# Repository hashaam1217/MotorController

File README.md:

# Cleaning up electronics

- Using Pin Sockets so we can reuse components
- We can switch between 8 and 64 Microsteps
-

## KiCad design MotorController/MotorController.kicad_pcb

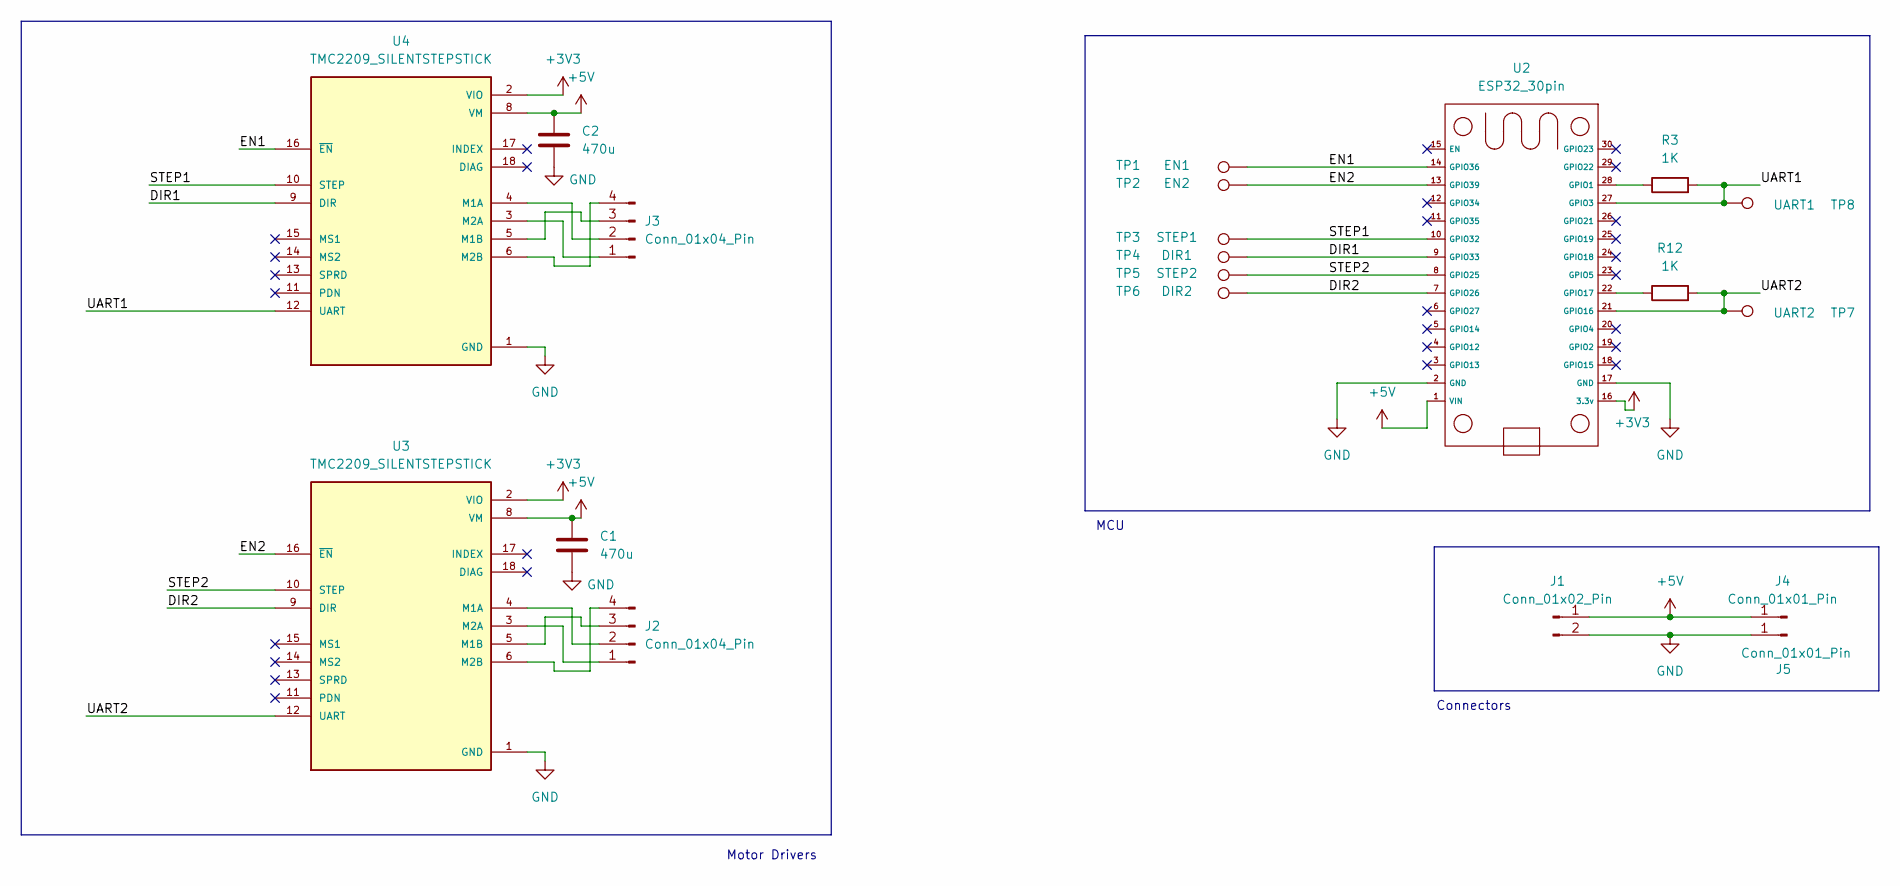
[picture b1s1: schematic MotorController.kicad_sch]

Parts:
C1, C2: 470u; CP_Radial_D6.3mm_P2.50mm
J1: Conn_01x02_Pin; PinSocket_1x02_P2.54mm_Vertical
J2, J3: Conn_01x04_Pin; PinHeader_1x04_P2.54mm_Vertical
J4, J5: Conn_01x01_Pin; PinSocket_1x01_P2.54mm_Vertical
R3, R12: 1K; R_Axial_DIN0617_L17.0mm_D6.0mm_P5.08mm_Vertical
TP1: EN1; TestPoint_Pad_2.0x2.0mm
TP2: EN2; TestPoint_Pad_2.0x2.0mm
TP3: STEP1; TestPoint_Pad_2.0x2.0mm
TP4: DIR1; TestPoint_Pad_2.0x2.0mm
TP5: STEP2; TestPoint_Pad_2.0x2.0mm
TP6: DIR2; TestPoint_Pad_2.0x2.0mm
TP7: UART2; TestPoint_Pad_2.0x2.0mm
TP8: UART1; TestPoint_Pad_2.0x2.0mm
U2: ESP32_30pin
U3, U4: TMC2209_SILENTSTEPSTICK; MODULE_TMC2209_SILENTSTEPSTICK; PARTREV 1.20

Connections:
+3V3: U2.16 (3.3v), U3.2 (VIO), U4.2 (VIO)
+5V: C1.1, C2.1, J1.1, J4.1 (Pin_1_1), U2.1 (VIN), U3.8 (VM), U4.8 (VM)
/DIR1: TP4.1 (1_1), U2.9 (GPIO33), U4.9 (DIR)
/DIR2: TP6.1 (1_1), U2.7 (GPIO26), U3.9 (DIR)
/EN1: TP1.1 (1_1), U2.14 (GPIO36), U4.16 (~EN)
/EN2: TP2.1 (1_1), U2.13 (GPIO39), U3.16 (~EN)
/STEP1: TP3.1 (1_1), U2.10 (GPIO32), U4.10 (STEP)
/STEP2: TP5.1 (1_1), U2.8 (GPIO25), U3.10 (STEP)
/UART1: R3.2, TP8.1 (1_1), U2.27 (GPIO3), U4.12 (UART)
/UART2: R12.2, TP7.1 (1_1), U2.21 (GPIO16), U3.12 (UART)
GND: C1.2, C2.2, J1.2, J5.1 (Pin_1_1), U2.2 (GND), U2.17 (GND), U3.1 (GND), U3.7 (GND), U4.1 (GND), U4.7 (GND)
unnamed: J2.1, U3.3 (M2A)
unnamed: J2.2, U3.4 (M1A)
unnamed: J2.3, U3.5 (M1B)
unnamed: J2.4, U3.6 (M2B)
unnamed: J3.1, U4.3 (M2A)
unnamed: J3.2, U4.4 (M1A)
unnamed: J3.3, U4.5 (M1B)
unnamed: J3.4, U4.6 (M2B)
unnamed: R3.1, U2.28 (GPIO1)
unnamed: R12.1, U2.22 (GPIO17)

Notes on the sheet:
Motor Drivers
MCU
Connectors

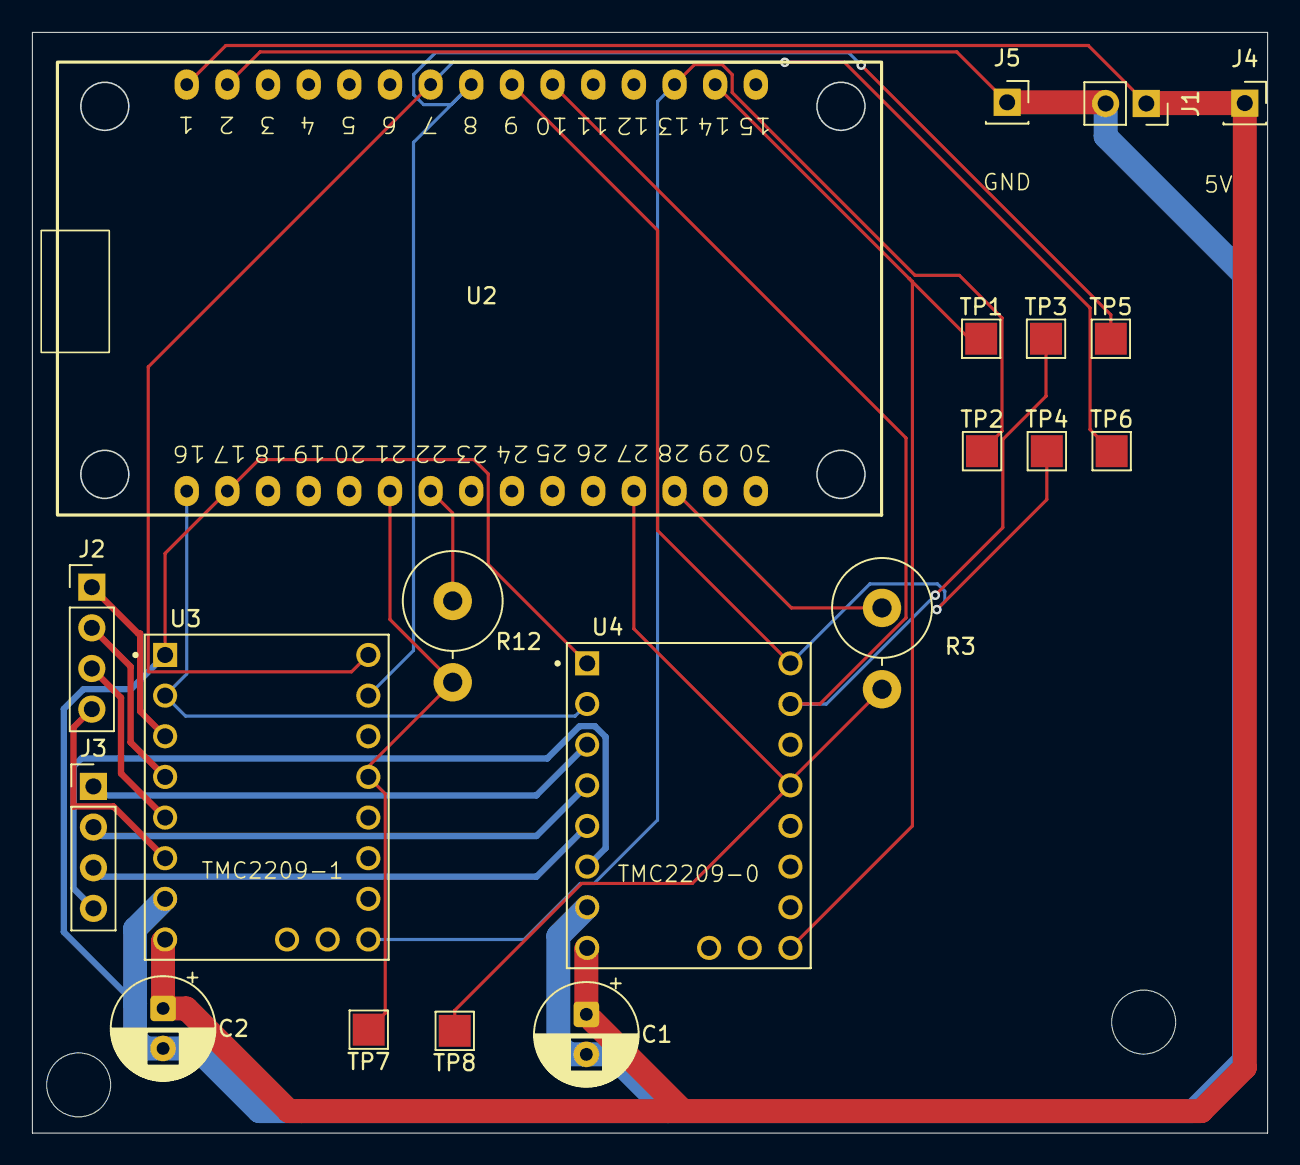
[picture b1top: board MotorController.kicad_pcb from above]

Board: 2 copper layers, 77.1 x 68.7 mm, 20 parts (0 on the bottom side), 21 nets.

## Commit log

2026-04-22 Waiting for breadboard
2026-04-29 2 Driver Design Done
